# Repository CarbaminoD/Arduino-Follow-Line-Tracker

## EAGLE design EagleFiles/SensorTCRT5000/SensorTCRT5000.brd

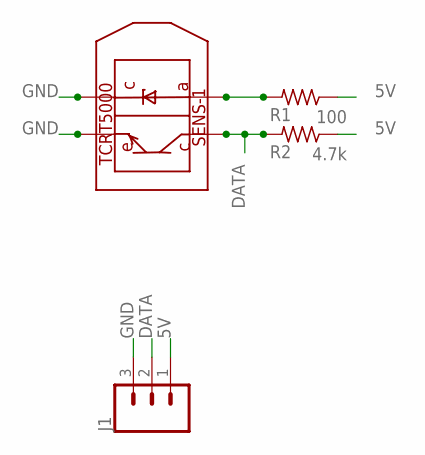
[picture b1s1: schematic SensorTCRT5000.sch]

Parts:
J1: CONN_03; 1X03
R1: 100; 0207/10
R2: 4.7k; 0207/10
SENS-1: TCRT5000; 5000

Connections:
5V: J1.1, R1.1, R2.1
DATA: J1.2, R2.2, SENS-1.P$1
GND: J1.3, SENS-1.P$2, SENS-1.P$4
unnamed: R1.2, SENS-1.P$3

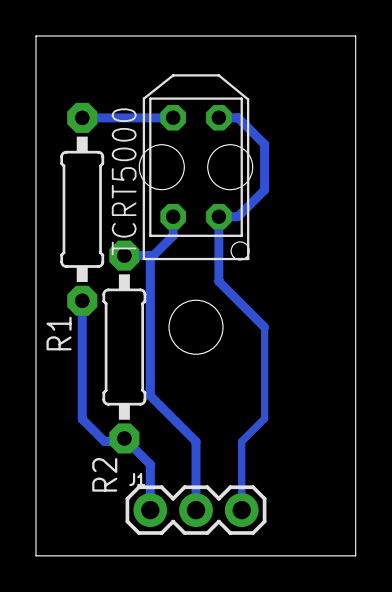
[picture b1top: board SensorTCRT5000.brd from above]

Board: 2 copper layers, 17.8 x 28.9 mm, 4 parts (0 on the bottom side), 4 nets.

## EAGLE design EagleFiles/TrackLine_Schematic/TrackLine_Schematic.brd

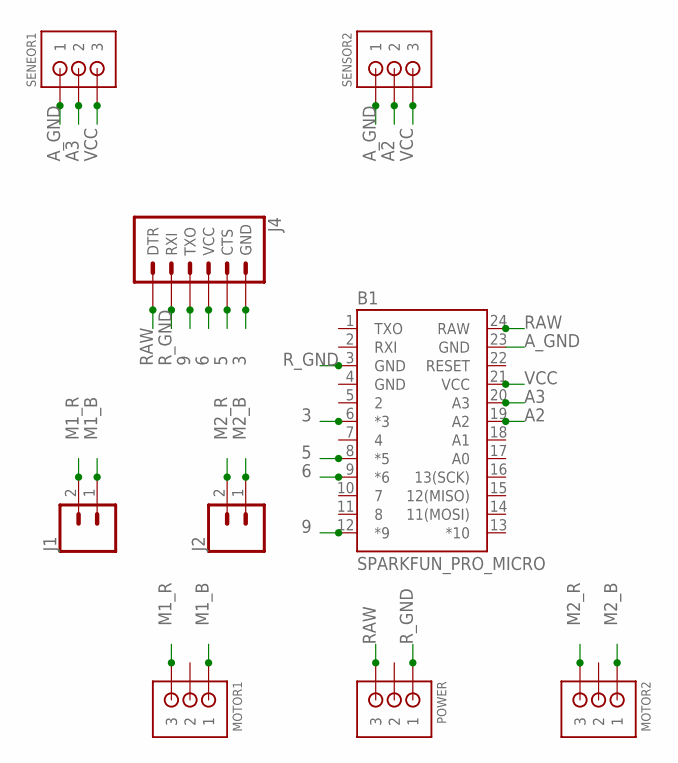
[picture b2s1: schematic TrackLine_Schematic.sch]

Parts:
B1: SPARKFUN_PRO_MICRO
J1, J2: CONN_025MM; SCREWTERMINAL-5MM-2
J4: 6_PIN_SERIAL_TARGET; 1X06
MOTOR1, MOTOR2: JST-PH_3-PIN_HEADER; JST_B3B-PH_HEADER
POWER: JST-PH_3-PIN_HEADER; JST_B3B-PH_HEADER
SENEOR1: JST-PH_3-PIN_HEADER; JST_B3B-PH_HEADER
SENSOR2: JST-PH_3-PIN_HEADER; JST_B3B-PH_HEADER

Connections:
3: B1.6 (*3), J4.6 (GND)
5: B1.8 (*5), J4.5 (CTS)
6: B1.9 (*6), J4.4 (VCC)
9: B1.12 (*9), J4.3 (TXO)
A2: B1.19 (A2), SENSOR2.P2 (2)
A3: B1.20 (A3), SENEOR1.P2 (2)
A_GND: B1.23 (GND), SENEOR1.P1 (1), SENSOR2.P1 (1)
GND: B1.4 (GND)
M1_B: J1.1, MOTOR1.P1 (1)
M1_R: J1.2, MOTOR1.P3 (3)
M2_B: J2.1, MOTOR2.P1 (1)
M2_R: J2.2, MOTOR2.P3 (3)
RAW: B1.24 (RAW), J4.1 (DTR), POWER.P3 (3)
R_GND: B1.3 (GND), J4.2 (RXI), POWER.P1 (1)
VCC: B1.21 (VCC), SENEOR1.P3 (3), SENSOR2.P3 (3)

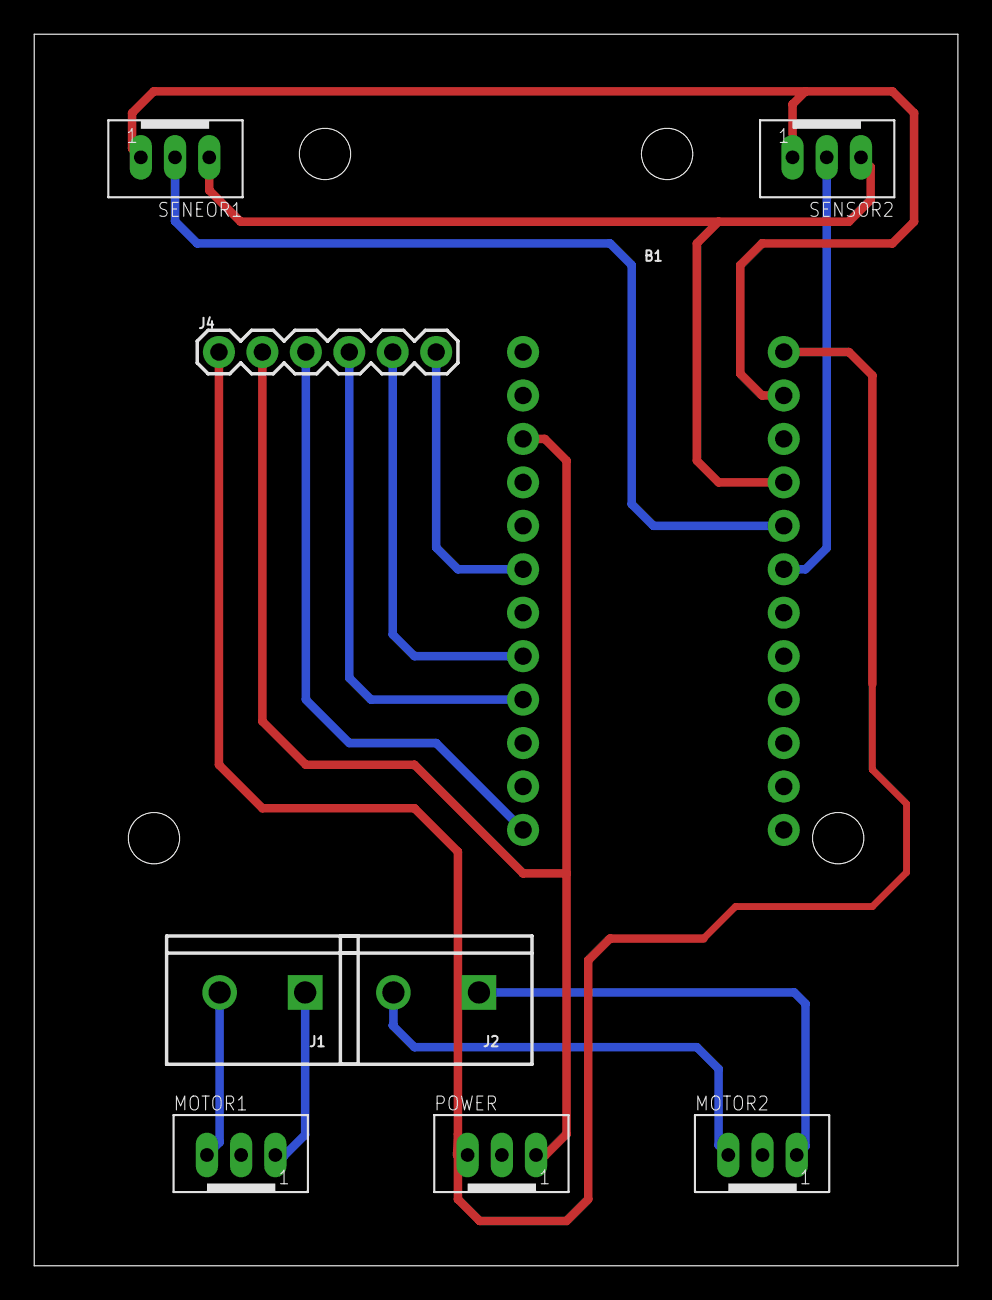
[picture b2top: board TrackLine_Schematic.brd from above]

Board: 2 copper layers, 54.0 x 72.0 mm, 9 parts (0 on the bottom side), 14 nets.

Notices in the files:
parts and their libraries:
SparkFun-Connectors: Licensing: Creative Commons ShareAlike 4.0 International - https://creativecommons.org/licenses/by-sa/4.0
